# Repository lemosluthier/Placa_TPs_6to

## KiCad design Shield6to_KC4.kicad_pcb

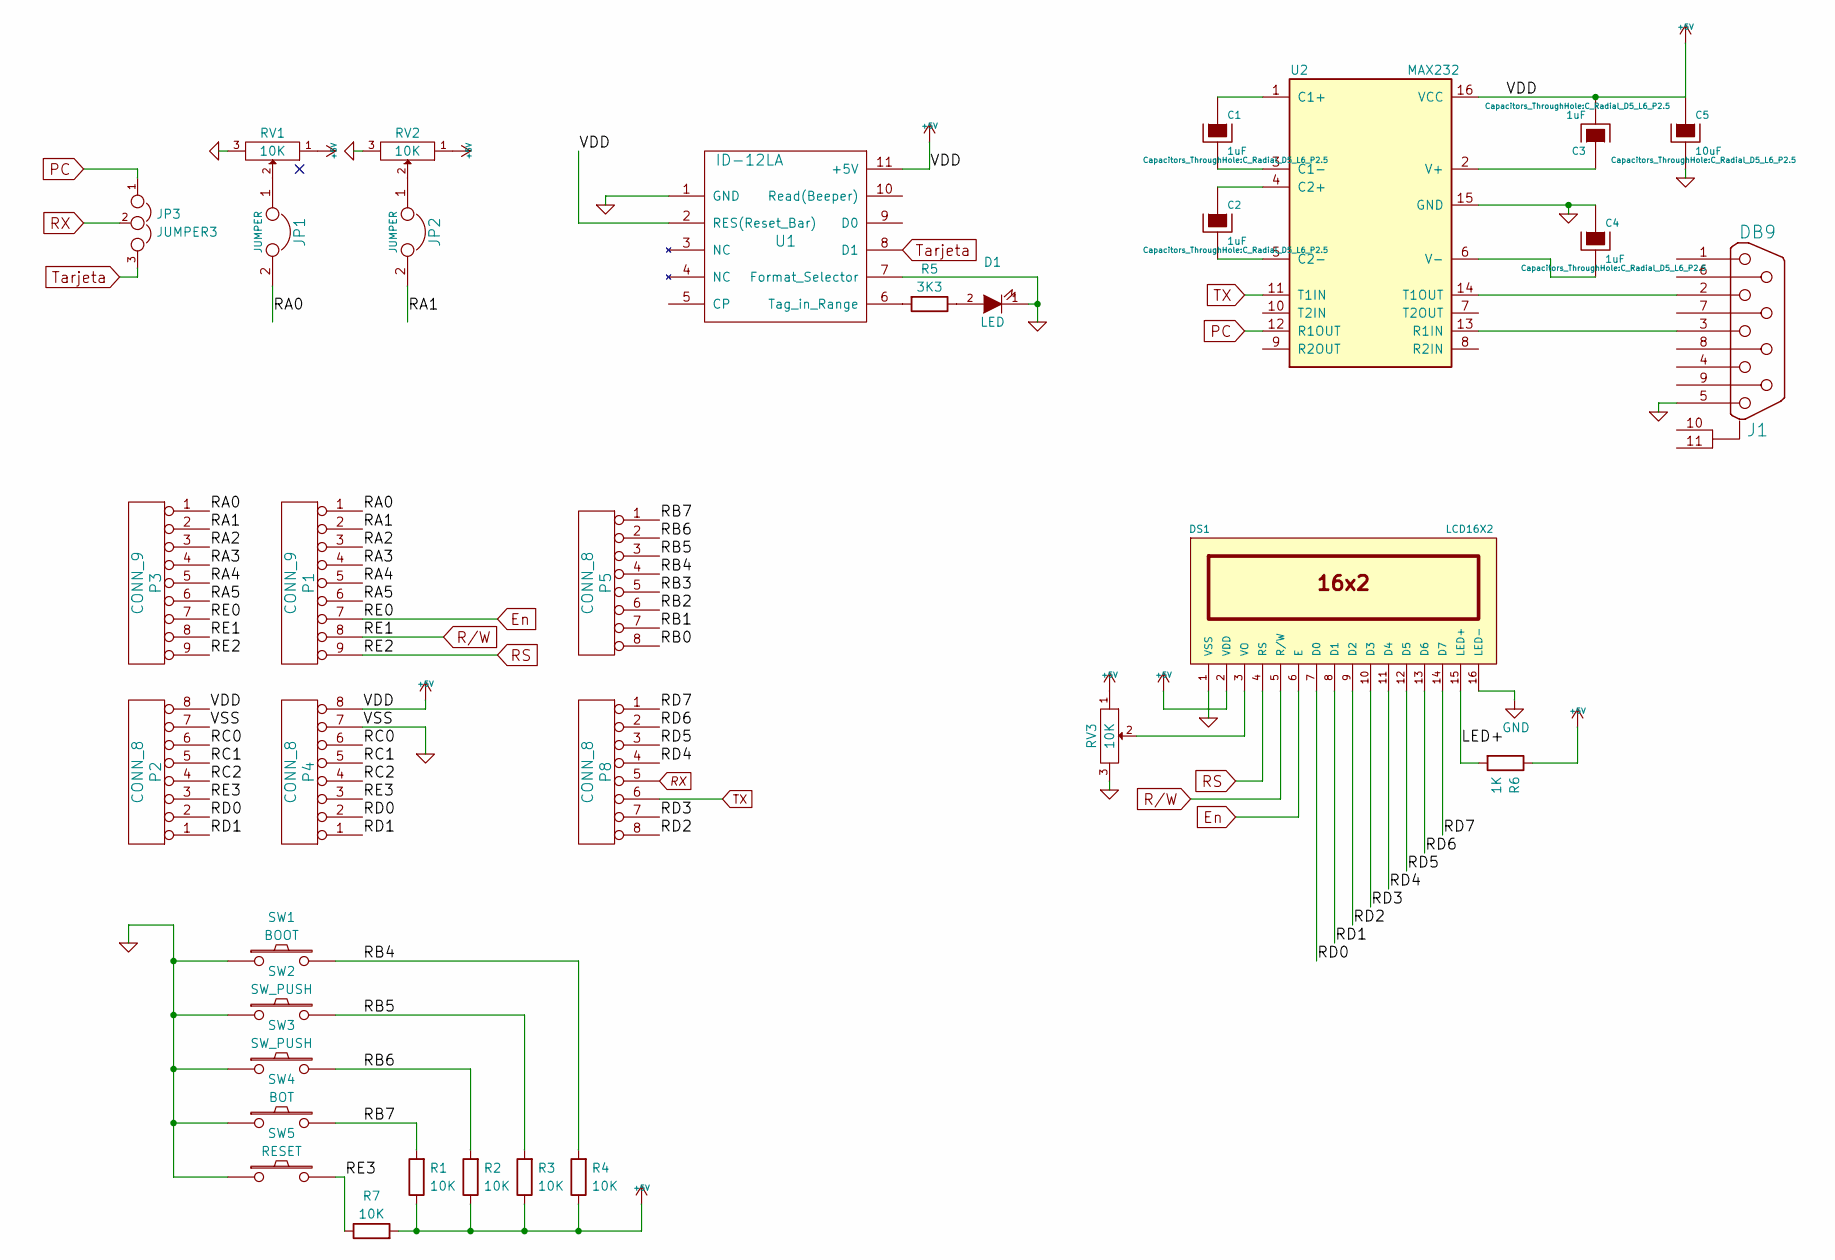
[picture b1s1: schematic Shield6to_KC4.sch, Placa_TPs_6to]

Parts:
C1, C2, C3, C4: 1uF; C_Radial_D5_L6_P2.5
C5: 10uF; C_Radial_D5_L6_P2.5
D1: LED; LED-3MM
DS1: LCD16X2; RC1602A
J1: DB9; DB9FC
JP1, JP2: JUMPER; Pin_Header_Straight_1x02
JP3: JUMPER3; Pin_Header_Straight_1x03
P1, P3: CONN_9; Socket_Strip_Straight_1x09
P2, P4, P5, P8: CONN_8; Socket_Strip_Straight_1x08
R1, R2, R3, R4, R7: 10K; Resistor_Horizontal_RM10mm
R5: 3K3; Resistor_Horizontal_RM10mm
R6: 1K; Resistor_Horizontal_RM10mm
RV1, RV2, RV3: 10K; Potentiometer_Bourns_3005_Angular_ScrewFront
SW1: BOOT; SW_PUSH_SMALL
SW2, SW3: SW_PUSH; SW_PUSH_SMALL
SW4: BOT; SW_PUSH_SMALL
SW5: RESET; SW_PUSH_SMALL
U1: ID-12LA; ID12-LA
U2: MAX232; DIP-16_W7.62mm

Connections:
+5V: C3.2, C5.1, DS1.2 (VDD), P2.8, P4.8, R1.1, R2.1, R3.1, R4.1, R6.1, R7.2, RV1.1, RV2.1, RV3.1, U1.2 (RES(Reset_Bar)), U1.11 (+5V), U2.16 (VCC)
/LED+: DS1.15 (LED+), R6.2
/RA0: JP1.2, P1.1, P3.1
/RA1: JP2.2, P1.2, P3.2
/RA2: P1.3, P3.3
/RA3: P1.4, P3.4
/RA4: P1.5, P3.5
/RA5: P1.6, P3.6
/RB0: P5.8
/RB1: P5.7
/RB2: P5.6
/RB3: P5.5
/RB4: P5.4, R4.2, SW1.2
/RB5: P5.3, R3.2, SW2.2
/RB6: P5.2, R2.2, SW3.2
/RB7: P5.1, R1.2, SW4.2
/RC0: P2.5, P4.5
/RC1: P2.4, P4.4
/RD0: DS1.7 (D0), P2.2, P4.2
/RD1: DS1.8 (D1), P2.1, P4.1
/RD2: DS1.9 (D2), P8.8
/RD3: DS1.10 (D3), P8.7
/RD4: DS1.11 (D4), P8.4
/RD5: DS1.12 (D5), P8.3
/RD6: DS1.13 (D6), P8.2
/RD7: DS1.14 (D7), P8.1
En: DS1.6 (E), P1.7, P3.7
GND: C4.1, C5.2, D1.1 (K), DS1.1 (VSS), DS1.16 (LED-), J1.5, J1.10 (GND), J1.11 (GND), P2.7, P4.7, RV1.3, RV2.3, RV3.3, SW1.1, SW2.1, SW3.1, SW4.1, SW5.1, U1.1 (GND), U1.7 (Format_Selector), U2.15 (GND)
unnamed: C1.1, U2.1 (C1+)
unnamed: C1.2, U2.3 (C1-)
unnamed: C2.1, U2.4 (C2+)
unnamed: C2.2, U2.5 (C2-)
unnamed: C3.1, U2.2 (V+)
unnamed: C4.2, U2.6 (V-)
unnamed: D1.2 (A), R5.1, R5.2, U1.6 (Tag_in_Range)
unnamed: DS1.3 (VO), RV3.2
unnamed: J1.2, U2.14 (T1OUT)
unnamed: J1.3, U2.13 (R1IN)
unnamed: JP1.1, RV1.2
unnamed: JP2.1, RV2.2
PC: JP3.1, U2.12 (R1OUT)
R/W: DS1.5 (R/W), P1.8, P3.8
RS: DS1.4 (RS), P1.9, P3.9
RX: JP3.2, P8.5
TX: P8.6, U2.11 (T1IN)
Tarjeta: JP3.3, U1.8 (D1)

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
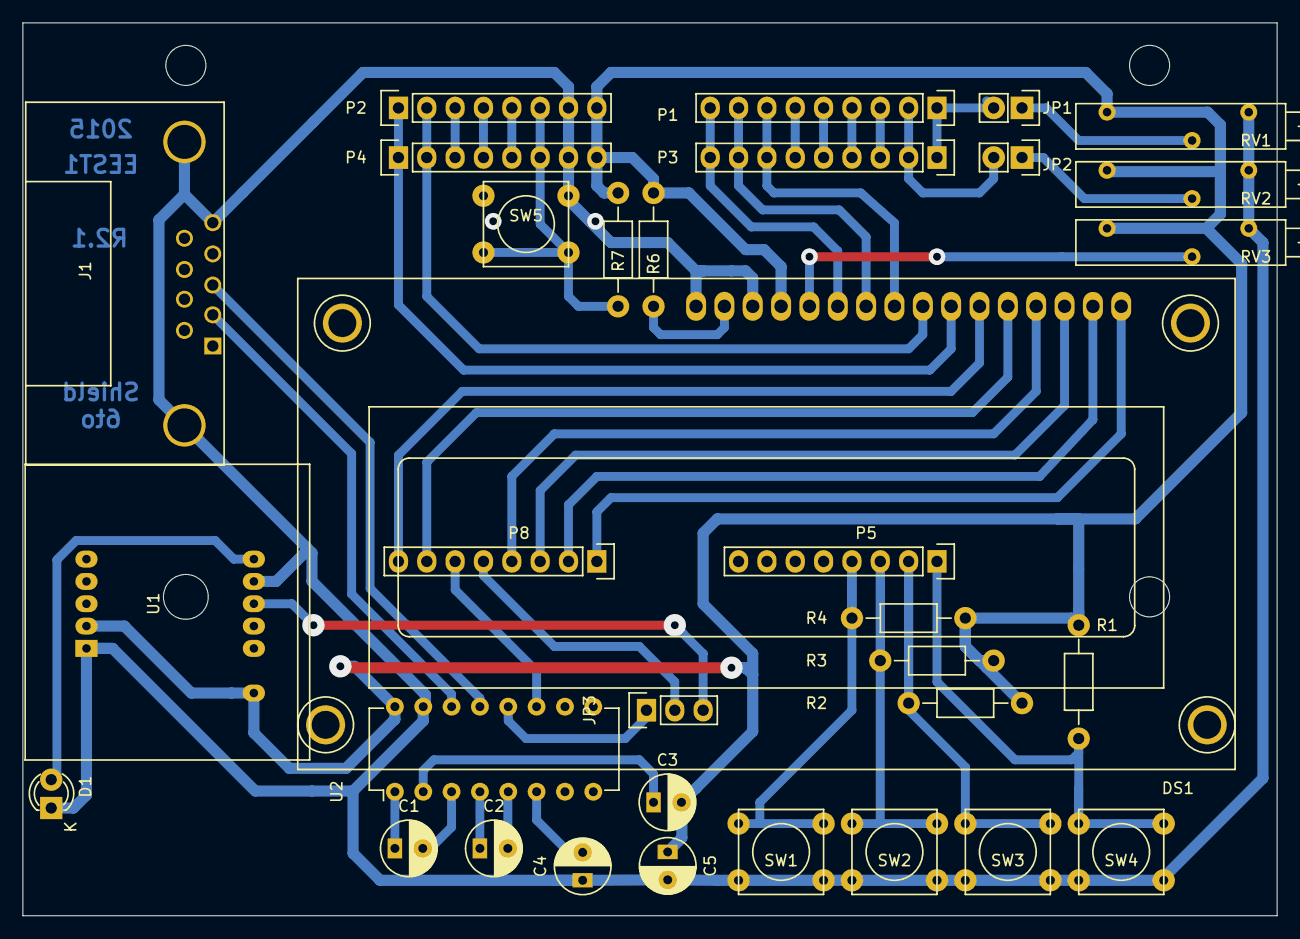
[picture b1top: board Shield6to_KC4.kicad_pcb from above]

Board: 2 copper layers, 112.4 x 80.0 mm, 33 parts (0 on the bottom side), 44 nets.

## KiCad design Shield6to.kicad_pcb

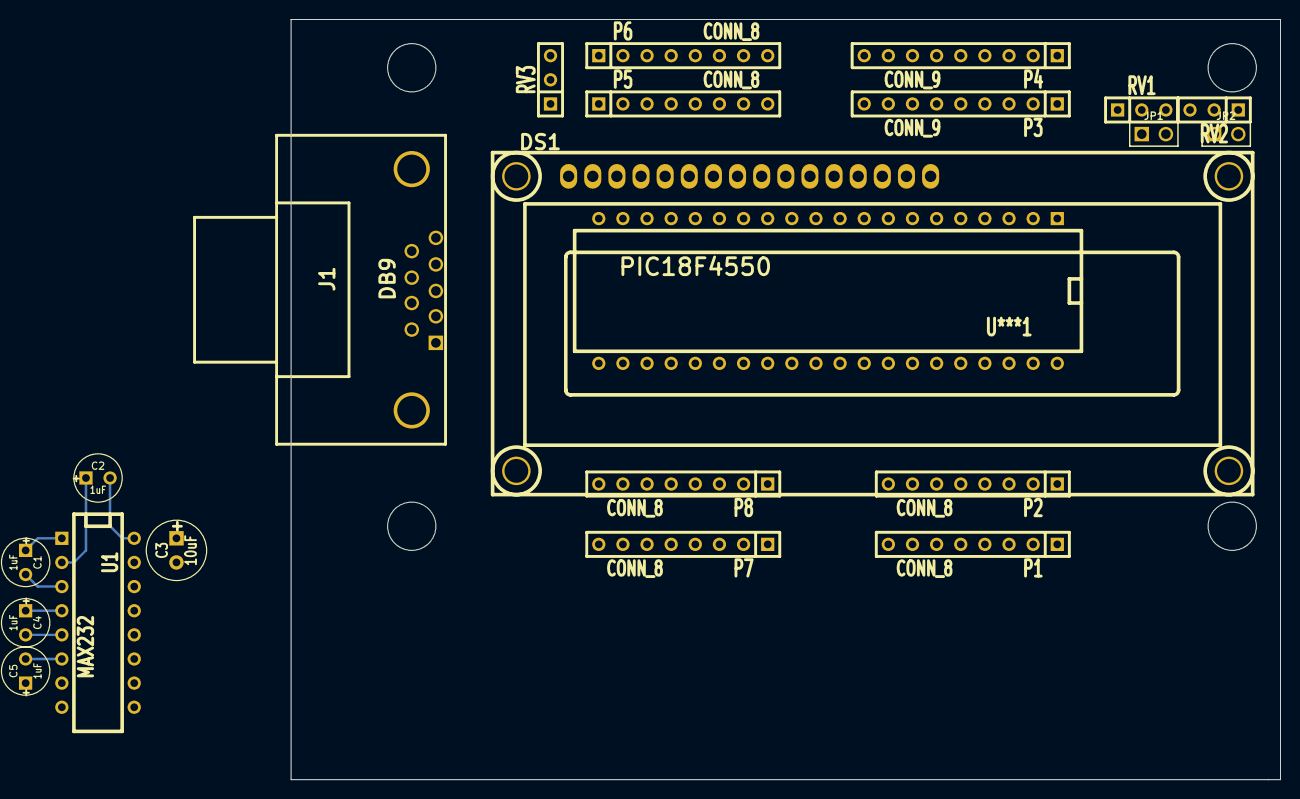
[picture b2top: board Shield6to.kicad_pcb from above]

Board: 2 copper layers, 104.1 x 80.0 mm, 22 parts (0 on the bottom side), 45 nets.

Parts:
C1, C2, C4, C5: 1uF; C1V5
C3: 10uF; C1V7
DS1: LCD16X2; WC1602A
J1: DB9; DB9FC
JP1, JP2: JUMPER; PIN_ARRAY_2X1
P1, P2, P5, P6, P7, P8: CONN_8; SIL-8
P3, P4: CONN_9; SIL-9
RV1, RV2, RV3: 10K; SIL-3
U1: MAX232; DIP-16__300
U***1: PIC18F4550; DIP-40__600

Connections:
+5V: C2.2, C3.1, DS1.2, RV1.1, RV2.1, RV3.1, U1.16, U***1.32
GND: C3.2, C5.1, DS1.1, J1.5, P5.7, P6.7, RV1.3, RV2.3, RV3.3, U1.15, U***1.12, U***1.31
unnamed: P5.3, P6.3, U***1.1
unnamed: P5.8, P6.8, U***1.11
unnamed: P5.6, P6.6, U***1.15
unnamed: P5.5, P6.5, U***1.16
unnamed: P5.4, P6.4, U***1.17
unnamed: DS1.7, P5.2, P6.2, U***1.19
unnamed: DS1.8, P5.1, P6.1, U***1.20
unnamed: J1.2, U1.14
unnamed: J1.3, U1.13
unnamed: C1.1, U1.1
unnamed: C1.2, U1.3
unnamed: C4.1, U1.4
unnamed: C4.2, U1.5
unnamed: C2.1, U1.2
unnamed: C5.2, U1.6
unnamed: DS1.3, RV3.2
unnamed: P1.5, P2.5, U***1.36
unnamed: P1.8, P2.8, U***1.33
unnamed: P1.7, P2.7, U***1.34
unnamed: P1.6, P2.6, U***1.35
unnamed: P1.4, P2.4, U***1.37
unnamed: P1.3, P2.3, U***1.38
unnamed: P1.2, P2.2, U***1.39
unnamed: P1.1, P2.1, U***1.40
unnamed: JP1.1, RV1.2
unnamed: DS1.13, P7.2, P8.2, U***1.29
unnamed: DS1.14, P7.1, P8.1, U***1.30
unnamed: P3.9, P4.9, U***1.10
unnamed: P3.8, P4.8, U***1.9
unnamed: P3.7, P4.7, U***1.8
unnamed: P3.6, P4.6, U***1.7
unnamed: P3.5, P4.5, U***1.6
unnamed: P3.4, P4.4, U***1.5
unnamed: P3.3, P4.3, U***1.4
unnamed: JP2.2, P3.2, P4.2, U***1.3
unnamed: JP1.2, P3.1, P4.1, U***1.2
unnamed: DS1.12, P7.3, P8.3, U***1.28
unnamed: DS1.9, P7.8, P8.8, U***1.21
unnamed: DS1.10, P7.7, P8.7, U***1.22
unnamed: DS1.11, P7.4, P8.4, U***1.27
unnamed: JP2.1, RV2.2
RX: P7.5, P8.5, U***1.26
TX: P7.6, P8.6, U1.11, U***1.25

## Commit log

2015-12-16 Committer: Esteban Lemos <esteban@mobile.lemos>
    On branch master
    Your branch is up-to-date with 'origin/master'.
    Changes to be committed:
    modified: Shield6to-cache.lib
    modified: Shield6to-rescue.lib
    modified: Shield6to.bak
2015-12-18 Changes to be committed: deleted: Shield6to-cache.lib deleted: Shield6to-rescue.lib deleted: Shield6to.cmp deleted: Shield6to.net modified: Shield6to_KC4-cache.lib renamed: Shield6to.sch -> Shield6to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
2015-12-20 Primera version de la Placa lista para la Revision de MArtín
2015-12-31 Changes to be committed: renamed: Librerias.pretty/ID12-LA.kicad_mod -> Modulos/ID12-LA.kicad_mod modified: Shield6to_KC4-cache.lib renamed: _saved_Shield6to_KC4.sch -> Shield6to_KC4.bak modified: Sh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
2015-12-31 Changes to be committed: modified: Shield6to_KC4_Con_RFID.kicad_pcb new file: Shield6to_KC4_Con_RFID.kicad_pcb-bak new file: Shield6to_KC4_Con_RFID.pro new file: Shield6to_KC4_SinRFID.pro
2016-02-09 Committer: Esteban Lemos <esteban@mobile.lemos>
    On branch master
    Your branch is up-to-date with 'origin/master'.
    Changes to be committed:
    deleted: Shield6to.kicad_pcb_sin_micro_1.kicad_pcb-bak
    deleted: Shield6to.kicad_pcb_sin_micro_1.pro
    deleted: Shield6to.pro
2016-03-06 new file: Modulos/SW_PUSH_SMALL.kicad_mod modified: Shield6to_KC4.kicad_pcb new file: Shield6to_KC4.kicad_pcb-bak modified: Shield6to_KC4.net new file: Shield6to_KC4_SinRFID.pro
2016-03-19 modified: Shield6to_KC4.kicad_pcb modified: Shield6to_KC4.kicad_pcb-bak modified: Shield6to_KC4.net new file: _saved_Shield6to_KC4.sch
2016-04-10 On branch master Your branch is up-to-date with 'origin/master'.
    Changes to be committed:
    modified: Shield6to_KC4.bak
    modified: Shield6to_KC4.kicad_pcb
    modified: Shield6to_KC4.kicad_pcb-bak
    modified: Shield6to_KC4.net
    modified: Shield6to_KC4.sch
2016-04-10 Changes to be committed: modified: Shield6to_KC4.kicad_pcb modified: Shield6to_KC4.kicad_pcb-bak
2016-05-10 Changes to be committed: new file: 3d_indicators.zip new file: Modelodelgabinete.fcstd new file: Modelodelgabinete.fcstd1 modified: Shield6to_KC4.bak modified: Shield6to_KC4.kicad_pcb modified: Shiel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
2016-05-16 Changes to be committed: modified: Modelodelgabinete.fcstd modified: Modelodelgabinete.fcstd1 new file: Modelodelgabinete2.fcstd new file: Modelodelgabinete2.fcstd1 modified: Shield6to_KC4.kicad_pcb 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
2016-06-14 Changes to be committed: modified: Modelodelgabinete.fcstd modified: Modelodelgabinete.fcstd1 new file: Modelodelgabinete3.fcstd new file: Modelodelgabinete4.fcstd new file: Modelodelgabinete4.fcstd1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
2016-06-24 Changes to be committed: new file: Autor.fcstd new file: Autor.fcstd1 new file: Ensamble.fcstd new file: Ensamble.fcstd.7293b8fa-8be1-474f-acef-e1659ffc93c6 modified: Modelodelgabinete5.fcstd new fil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
